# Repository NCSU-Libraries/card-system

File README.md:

# Card System
Regulates access to DH Hill Library Makerspace, restricted to NC State University students, faculty and staff with campus ID cards. 

This repository includes Python code running on the system as well as electrical and mechanical design files.

## System Overview

The system comprises a Raspberry Pi with touchscreen, magnetic stripe card readers, a laser-cut enclosure produced in-house, a circuit board produced in-house, and associated electronics. It interacts with a web API (also produced in the Library) to authenticate users. The Pi runs a modified version of Raspbian Linux provided by Adafruit for use with their PiTFT touchscreens.

Users sign into the space by swiping their campus ID card on the entry card reader. The system accesses a database of users with the SpaceAuth API to check for the user's access privileges. If the user has access, they are greeted with a green light and an "access granted" from the speaker; otherwise, a red light and "access denied". The system also has a motion sensor (PIR) which, when triggered, triggers the system to deny access.

## Bill of Materials
| Item  | Quantity  | Link  |
| ----- | --------- | ----- |
Raspberry Pi 2 Model B | 1 | https://www.raspberrypi.org/products/raspberry-pi-2-model-b/
PiTFT Plus 3.5" 480x320 | 1 | https://www.adafruit.com/products/2441
Assorted Terminal Blocks | - | https://www.adafruit.com/products/2234
ID TECH MiniMag Duo IDMB-354133B | 2 | http://idtechproducts.com/products/swipe-reader-writers/minimag-ii-compact-intelligent-magstripe-reader
Panel Monunt USB Port | 3 | https://www.adafruit.com/product/908
Panel Mount Ethernet Port | 1 | https://www.adafruit.com/products/909
Panel Mount 2.1mm Barrel Jack | 1 | https://www.adafruit.com/products/610
PIR Sensor | 1 | https://www.adafruit.com/products/189
330R Resistors | 2 | https://www.sparkfun.com/products/11507
10mm Green LED | 1 | https://www.sparkfun.com/products/10633
10mm Red LED | 1 | https://www.sparkfun.com/products/10632
3" 8 Ohm Speaker | 1 | https://www.adafruit.com/products/1313
3.5mm Stereo Plug | 1 | https://www.adafruit.com/products/1700
Mono Amplifier | 1 | https://www.sparkfun.com/products/11044
10K Logarithmic Potentiometer | 1 | https://www.sparkfun.com/products/9940
Male Machine Pin Headers | 1 | https://www.sparkfun.com/products/117
Female Machine Pin Headers | 1 | https://www.sparkfun.com/products/743
2x13 shrouded header | 1 | https://www.sparkfun.com/products/retired/11490
6-wire Ribbon Cable | 1 | https://www.sparkfun.com/products/10651
2x6 Crimp connector | 2 | https://www.sparkfun.com/products/10651
2x6 Shrouded Header | 1 | https://www.sparkfun.com/products/10877

## Author
Aaron Arthur, adarthur@ncsu.edu

## Project Collaborators
Bret Davidson  (author of Space Auth API)

Adam Rogers (project requirements + management)

Jack Twiddy (PCB and enclosure fabrication)

Augustus Vieweg (code contribution)

## LICENSE
MIT License

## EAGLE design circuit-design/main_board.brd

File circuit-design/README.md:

#Circuit Design
##Main Board Schematic

##Main Board Layout

##Ribbon to FTDI Schematic

##Ribbon to FTDI Layout

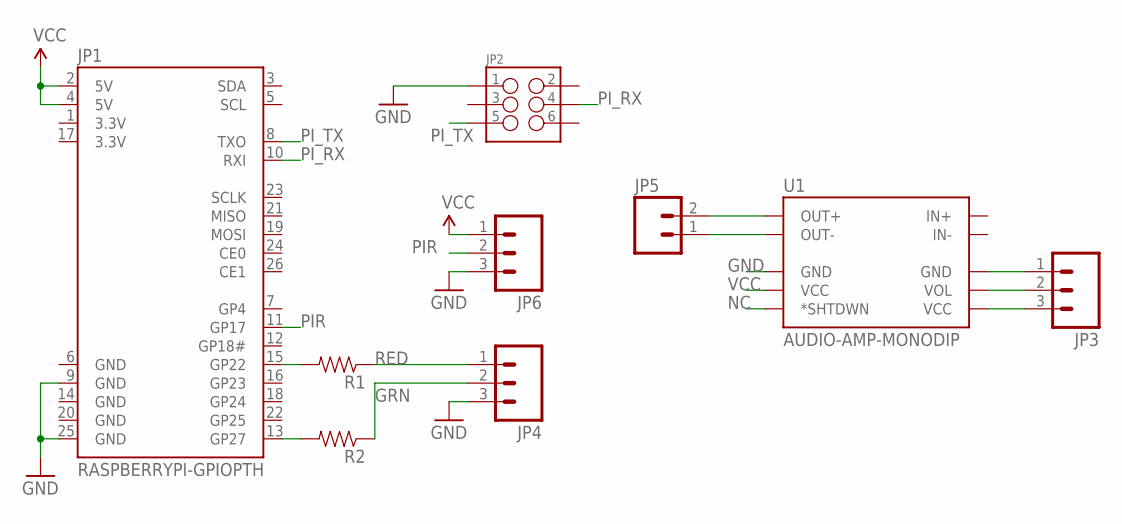
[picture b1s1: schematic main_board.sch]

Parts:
JP1: RASPBERRYPI-GPIOPTH; 2X13-SHROUDED
JP2: M03X2SHROUD; 2X3-SHROUDED
JP3, JP4, JP6: M03PTH; 1X03
JP5: M021X02_NO_SILK; 1X02_NO_SILK
R1, R2: RESISTORPTH-1/4W; AXIAL-0.4
U1: AUDIO-AMP-MONODIP; AUDIO-AMP-MONO

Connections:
3.3V: JP1.1 (3.3V), JP1.17 (3.3V)
GND: JP1.6 (GND), JP1.9 (GND), JP1.14 (GND), JP1.20 (GND), JP1.25 (GND), JP2.1, JP4.3, JP6.3, U1.PWR- (GND)
GRN: JP4.2, R2.P$1 (1)
unnamed: JP5.2, U1.OUT+
unnamed: JP5.1, U1.OUT-
unnamed: JP1.15 (GP22), R1.P$2 (2)
unnamed: JP1.13 (GP27), R2.P$2 (2)
unnamed: JP3.1, U1.VOL- (GND)
unnamed: JP3.2, U1.VOL
unnamed: JP3.3, U1.VOL+ (VCC)
NC: U1.S (*SHTDWN)
PIR: JP1.11 (GP17), JP6.2
PI_RX: JP1.10 (RXI), JP2.4
PI_TX: JP1.8 (TXO), JP2.5
RED: JP4.1, R1.P$1 (1)
VCC: JP1.2 (5V), JP1.4 (5V), JP6.1, U1.PWR+ (VCC)

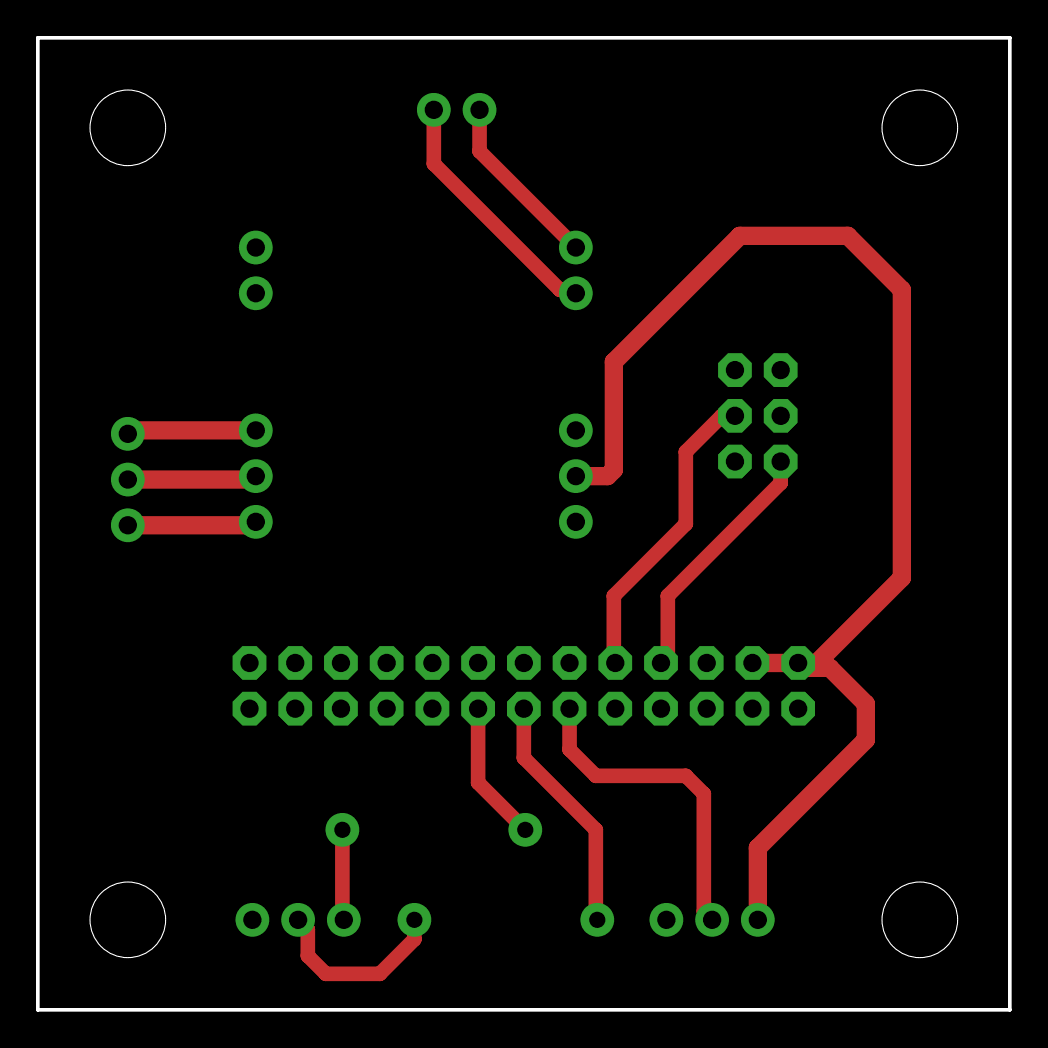
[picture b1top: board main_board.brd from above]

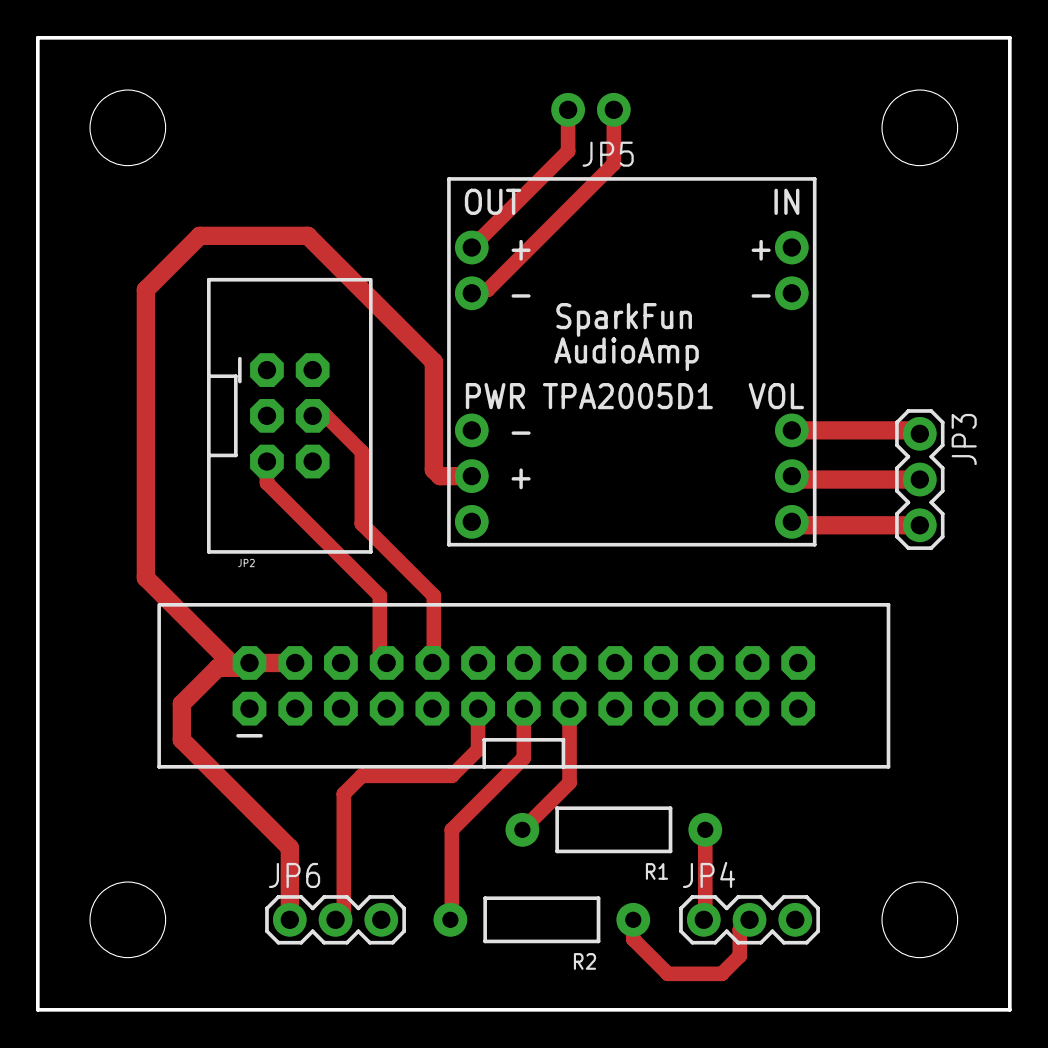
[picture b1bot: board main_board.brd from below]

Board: 2 copper layers, 54.0 x 54.0 mm, 9 parts (9 on the bottom side), 15 nets.

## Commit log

2016-07-26 Update README.md
    updated card reader model #
2017-07-21 Fixes formatting issue

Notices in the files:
parts and their libraries:
SparkFun-Boards: Licensing: Creative Commons ShareAlike 4.0 International - https://creativecommons.org/licenses/by-sa/4.0
